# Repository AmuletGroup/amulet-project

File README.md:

The Amulet Project
=====

**The Amulet Project** envisions computational jewelry, in the form of a bracelet or pendant, that provide the properties essential for successful body-area mHealth networks. These devices coordinate the activity of the body-area network and provide a discreet means for communicating with their wearer. Such devices complement the capabilities of a smartphone, bridging the gap between the type of pervasive computing possible with a mobile phone and that enabled by wearable computing. Find more information on the [Amulet Project Website](https://amulet-project.org/)

**The Amulet Platform** is a major step towards fulfilling this vision. The generalized platform is comprised of hardware and software for developing energy- and resource-efficient applications on multi-application wearable devices. This includes:

- the Amulet Firmware Toolchain
- the Amulet Runtime
- the ARP-View energy prediction and insight graphical tool ([check out a demo here](https://arpview.herokuapp.com))
- open reference hardware.

Amulet allows developers to interactively explore how their implementation decisions impact battery life without the need for hardware modeling and additional software development. **Amulet represents a new approach to developing long-lived wearable applications.** We envision the Amulet Platform enabling long-duration experiments on human subjects in a wide variety of studies.

We also aim to equip the health-behavior science community with a wearable platform researchers can field for long-duration experiments on human subjects in a wide variety of studies, by providing the entire Amulet Platform as an open-source, open-hardware alternative to the available commercial platforms that have so far been used for wearables research. 
We envision the Amulet Platform as being broadly applicable to those in the sensing communities, as well as domain scientists and practitioners in human-centered fields like health and fitness. With the Amulet Platform, sensor researchers can prototype new wearable devices and test new sensing technology without building from scratch.

---

### Getting Started
To learn how to obtain hardware, setup your dev environment, and program an Amulet refer to [this](GETTING_STARTED.md) guide.

---

### Contributors and Acknowledgements
Amulet is an ongoing collaboration between Dartmouth College and Clemson University.

**Dartmouth College:**

- Ryan Halter (Engineering): Co-PI; Assistant Professor of Engineering.
- David Kotz (Computer Science): Principal Investigator; Professor of Computer Science.
- John Batsis (Geisel School Of Medicine)
- Taylor Hardin (Computer Science): graduate student.
- Sarah Lord (Psychiatric Research Center)
- Jasmine Mai (Computer Science): undergraduate student.
- Varun Mishra (Computer Science): graduate student.
- Patrick Proctor (Computer Science): programmer.
- Ron Peterson (Computer Science): senior programmer.
- Gunnar Pope (Engineering): graduate student.

**Clemson University:**

- Kelly Caine (Human Centered Computing): Co-PI; Assistant Professor of Human-Centered Computing.
- Josiah Hester (Computer Science): graduate student, now at Northwestern.
- Vivian Motti (Human Centered Computing): now at George Mason University.
- Ryan Scott (Computer Science: Graduate Student.
- Jacob Sorber (Computer Science): PI; Assistant Professor of Computer Science.
- Byron Lowens (Human Centered Computing): graduate student.

**Former members:**

- George Boateng (Engineering): graduate student; now at ETH Zurich.
- Eric Chen (Computer Science): undergraduate student.
- Kevin Freeman (Computer Science): graduate student.
- Bhargav Golla (Computer Science): graduate student.
- Emily Greene (Computer Science): undergraduate student; now at Amazon.
- Steven Hearndon (Computer Science): graduate student.
- Hilary Johnson (Engineering): undergraduate student.
- Anna Knowles (Computer Science): undergraduate student.
- Andrés Molina-Markham (Computer Science); now at RSA Labs.
- Emma Oberstein (Computer Science): undergraduate student.
- Travis Peters (Computer Science): graduate student.
- Joseph Skinner (Engineering): technician.
- Tianlong Yun (Computer Science): now at Google.

This research results from a research program at the Institute for Security, Technology, and Society, supported by the National Science Foundation under award numbers CNS- 1314281, CNS-1314342, and TC-0910842, and by the Department of Health and Human Services (SHARP program) under award number 90TR0003-01. The views and conclusions contained in this document are those of the authors and should not be interpreted as necessarily representing the official policies, either expressed or implied, of the sponsors.

---
### License

```
Copyright 2016 by the Trustees of Dartmouth College and Clemson University, 
and distributed under the terms of the "Dartmouth College Non-Exclusive Research
Use Source Code License Agreement" (for NON-COMMERCIAL research purposes only), 
as detailed in a file named LICENSE.pdf within this repository.
```
[Please find our full license here.](LICENSE.pdf)

---
### Attribution

Please find a list of software used in the development of Amulet [here.](ATTRIBUTION.md)

---
### Issues

Please use Github's Issue tracking software to submit any issues or concerns regarding Amulet software or hardware.

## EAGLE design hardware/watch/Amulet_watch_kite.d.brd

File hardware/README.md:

Hardware
===
The Amulet wearable prototype is mostly a single-board system. 
The main board, battery, haptic buzzer, and secondary storage board are all housed in a custom-designed 3D-printed case that fits a standard 20mm off-the-shelf watchband.

#### Features
- **Processing**: 
  - Texas Instruments MSP430FR5989, 2 KB SRAM and 128 KB of FRAM
- **Sensing**: 
  - Analog Devices ADMP510 microphone
  - Everlight ALS-PT19 light sensor
  - Texas Instruments TMP20 temperature sensor
  - STMicroelectronics LSM6DSL gyroscope
  - Analog Devices ADXL362 accelerometer
  - Lapis Semi ML8511 UVA/B sensor
- **Communication**: 
  - Nordic nRF51822 used as a modem for communicating with peripheral BLE devices (such as a heart-rate monitor)
- **User Interface**: 
  - Sharp LS013B7DH03 display with 128x128 resolution
  - Two buttons
  - Three capacitive touch sensors with low power MPR121 touch controller
  - Haptic buzzer, and two LEDs.
- **Storage**:  
 - The small secondary storage board holds a microSD card reader. 
- **Misc**:
  - The board also includes a battery charger (MCP73831)
  - 110mAh battery

### Getting an Amulet
You can build your own using the hardware files provided or request pre-built Amulet's from us by contacting rapjr@cs.dartmouth.edu. If you are part of a research lab we will generally accept your request.

### Assembling an Amulet
Refer to [this](../media/Amulet_DC_kitec_assembly.pdf) guide for assembling the Amulet companion board, and [this](../media/Amulet_kitec_case_assembly.pdf) guide for placing an amulet in a case.

### Programming an Amulet
[Refer to this guide for how to set up your dev environment and program an amulet.](../GETTING_STARTED.md)

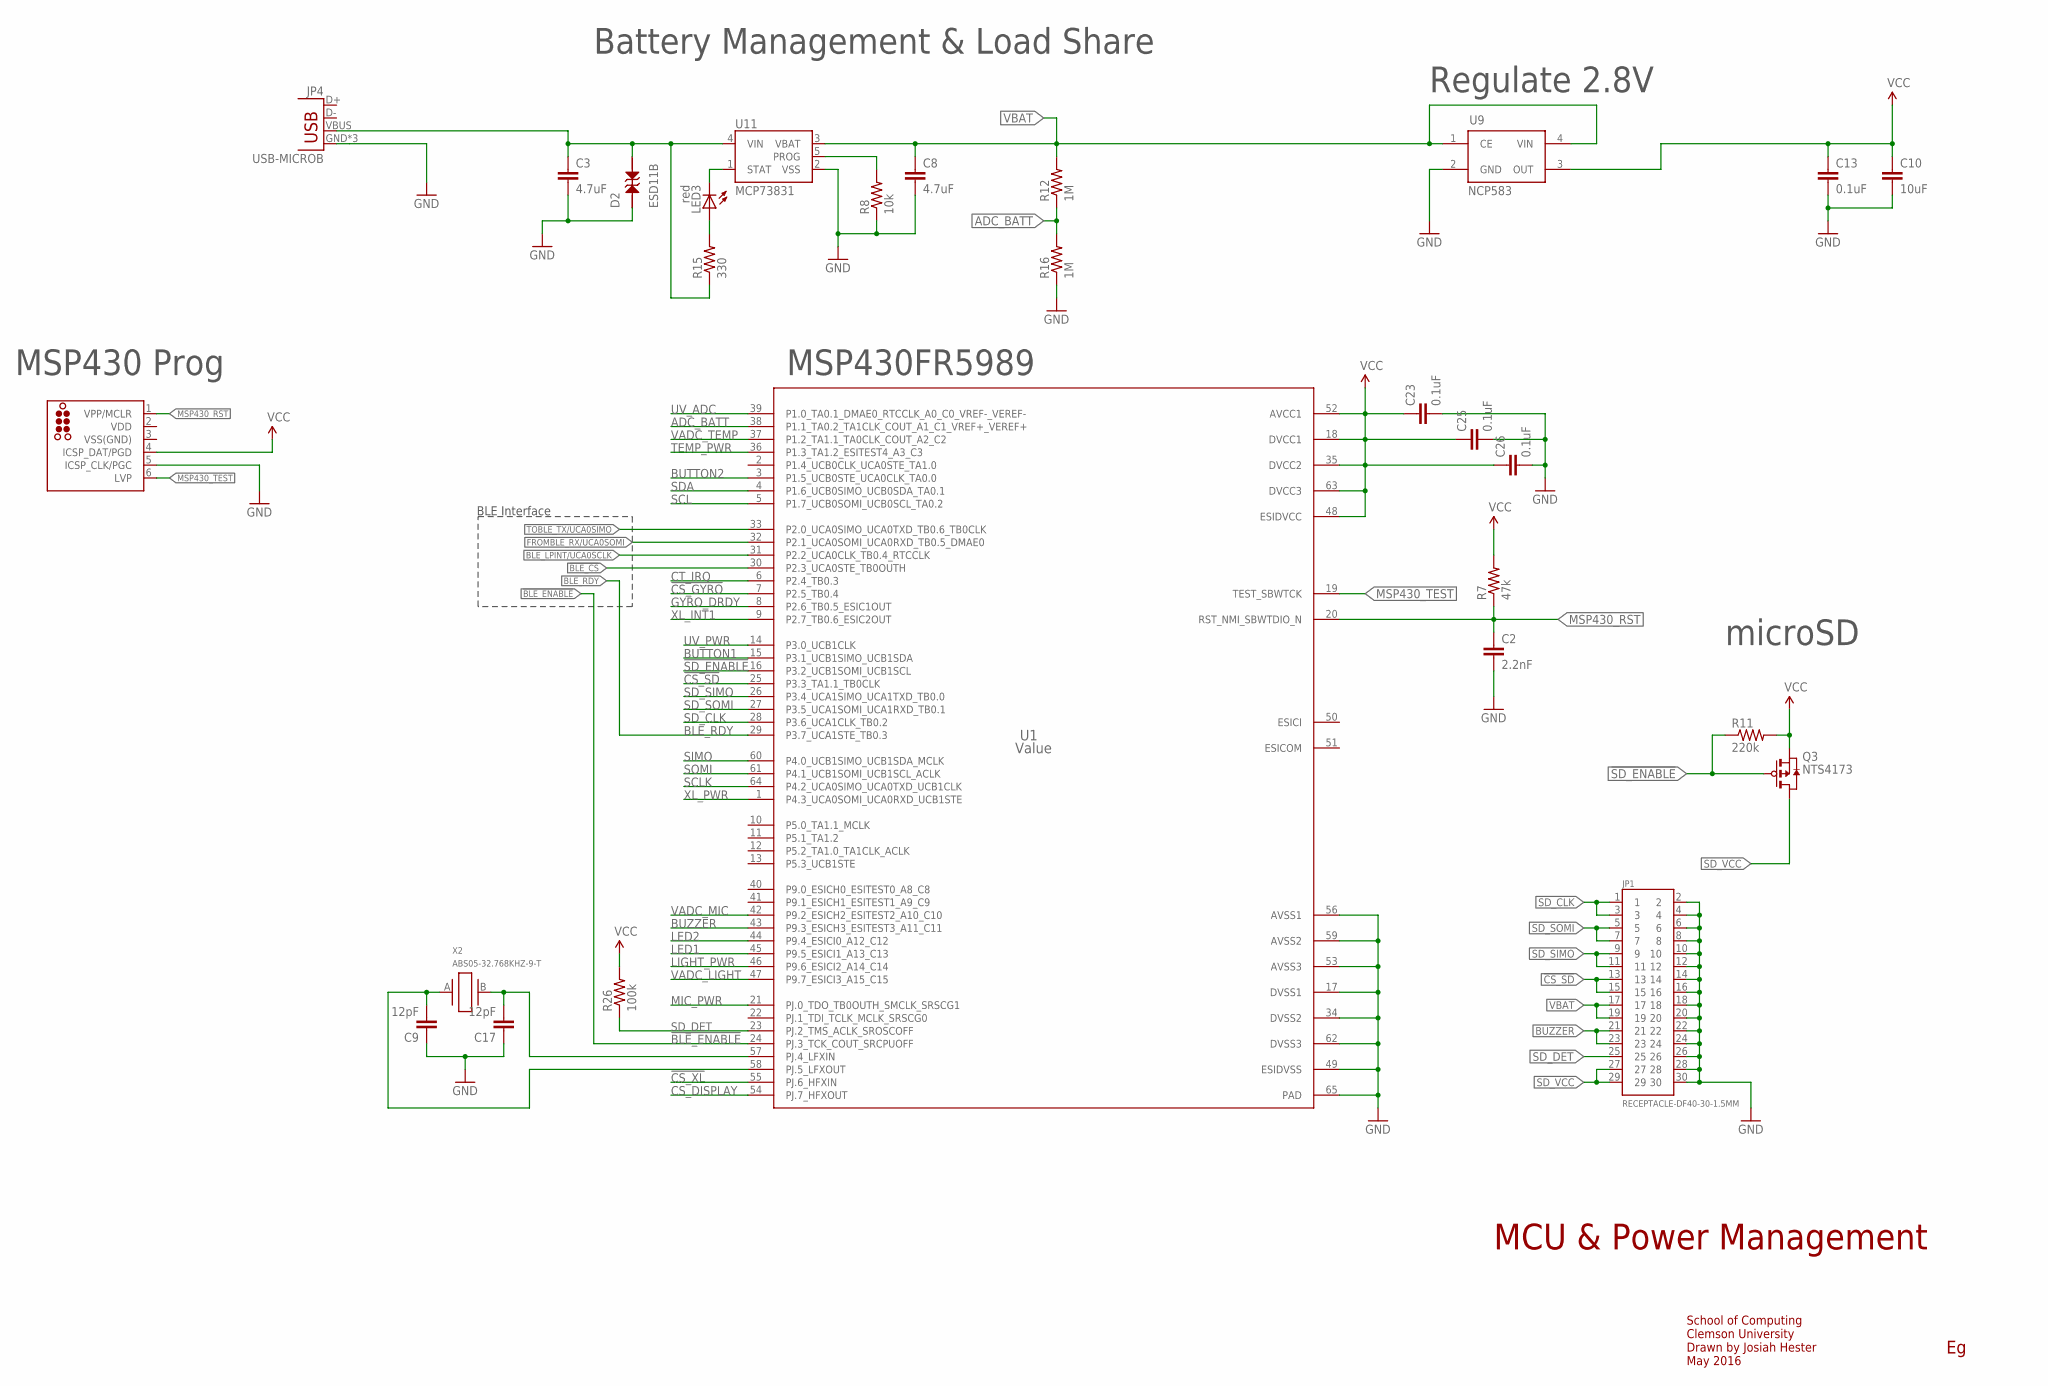
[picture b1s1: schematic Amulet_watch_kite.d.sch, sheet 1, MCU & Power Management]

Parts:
C2: 2.2nF; 0402
C3, C8: 4.7uF; 0805
C9, C17: 12pF; 0402
C10: 10uF; 0805
C13, C23, C25, C26: 0.1uF; 0402
D2: ESD11B; DSN2
J1: TC2030-MCP-NL
JP1: RECEPTACLE-DF40-30-1.5MM
JP4: USB-MICROB
LED3: red; LED-0603
Q3: NTS4173; SC-70-3
R7: 47k; 0402
R8: 10k; 0402
R11: 220k; 0402; DIGIKEY RHM12.0KCDCT-ND
R12, R16: 1M; 0402
R15: 330; 0402
R26: 100k; 0402
U1: Value; RGC0064B; DIGIKEY 296-42031-1-ND
U9: NCP583; SC82-AB_1PRIMARY
U11: MCP73831; SOT23-5
X2: ABS05-32.768KHZ-9-T; ABS05

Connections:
!BLE_CS: U1.30 (P2.3_UCA0STE_TB0OUTH); also elsewhere on the board
!BLE_ENABLE: U1.24 (PJ.3_TCK_COUT_SRCPUOFF); also elsewhere on the board
!CS_GYRO: U1.7 (P2.5_TB0.4); also elsewhere on the board
!CS_SD: JP1.13, JP1.15, U1.25 (P3.3_TA1.1_TB0CLK)
!CS_XL: U1.55 (PJ.6_HFXIN); also elsewhere on the board
!SD_ENABLE: Q3.P1 (G), R11.1, U1.16 (P3.2_UCB1SOMI_UCB1SCL)
ADC_BATT: R12.1, R16.2, U1.38 (P1.1_TA0.2_TA1CLK_COUT_A1_C1_VREF+_VERE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)
BLE_LPINT/UCA0SCLK: U1.31 (P2.2_UCA0CLK_TB0.4_RTCCLK); also elsewhere on the board
BLE_RDY: U1.29 (P3.7_UCA1STE_TB0.3); also elsewhere on the board
BUTTON1: U1.15 (P3.1_UCB1SIMO_UCB1SDA); also elsewhere on the board
BUTTON2: U1.3 (P1.5_UCB0STE_UCA0CLK_TA0.0); also elsewhere on the board
BUZZER: JP1.21, JP1.23, U1.43 (P9.3_ESICH3_ESITEST3_A11_C11)
CS_DISPLAY: U1.54 (PJ.7_HFXOUT); also elsewhere on the board
CT_IRQ: U1.6 (P2.4_TB0.3); also elsewhere on the board
FROMBLE_RX/UCA0SOMI: U1.32 (P2.1_UCA0SOMI_UCA0RXD_TB0.5_DMAE0); also elsewhere on the board
GND: C2.2, C3.2, C8.2, C9.1, C10.2, C13.2, C17.1, C23.2, C25.2, C26.2, D2.P$1 (1), J1.5 (ICSP_CLK/PGC), JP1.2, JP1.4, JP1.6, JP1.8, JP1.10, JP1.12, JP1.14, JP1.16, JP1.18, JP1.20, JP1.22, JP1.24, JP1.26, JP1.28, JP1.30, JP4.GND, JP4.MT1 (GND), JP4.MT2 (GND), R8.1, R16.1, U1.17 (DVSS1), U1.34 (DVSS2), U1.49 (ESIDVSS), U1.53 (AVSS3), U1.56 (AVSS1), U1.59 (AVSS2), U1.62 (DVSS3), U1.65 (PAD), U9.2 (GND), U11.2 (VSS); also elsewhere on the board
GYRO_DRDY: U1.8 (P2.6_TB0.5_ESIC1OUT); also elsewhere on the board
LED1: U1.45 (P9.5_ESICI1_A13_C13); also elsewhere on the board
LED2: U1.44 (P9.4_ESICI0_A12_C12); also elsewhere on the board
LIGHT_PWR: U1.46 (P9.6_ESICI2_A14_C14); also elsewhere on the board
MIC_PWR: U1.21 (PJ.0_TDO_TB0OUTH_SMCLK_SRSCG1); also elsewhere on the board
MSP430_RST: C2.1, J1.1 (VPP/MCLR), R7.1, U1.20 (RST_NMI_SBWTDIO_N); also elsewhere on the board
MSP430_TEST: J1.6 (LVP), U1.19 (TEST_SBWTCK)
unnamed: R8.2, U11.5 (PROG)
unnamed: C17.2, U1.57 (PJ.4_LFXIN), X2.B (2)
unnamed: C9.2, U1.58 (PJ.5_LFXOUT), X2.A (1)
unnamed: LED3.C, U11.1 (STAT)
unnamed: LED3.A, R15.2
SCL: U1.5 (P1.7_UCB0SOMI_UCB0SCL_TA0.2); also elsewhere on the board
SCLK: U1.64 (P4.2_UCA0SIMO_UCA0TXD_UCB1CLK); also elsewhere on the board
SDA: U1.4 (P1.6_UCB0SIMO_UCB0SDA_TA0.1); also elsewhere on the board
SD_CLK: JP1.1, JP1.3, U1.28 (P3.6_UCA1CLK_TB0.2)
SD_DET: JP1.25, R26.1, U1.23 (PJ.2_TMS_ACLK_SROSCOFF)
SD_SIMO: JP1.9, JP1.11, U1.26 (P3.4_UCA1SIMO_UCA1TXD_TB0.0)
SD_SOMI: JP1.5, JP1.7, U1.27 (P3.5_UCA1SOMI_UCA1RXD_TB0.1)
SD_VCC: JP1.27, JP1.29, Q3.P3 (D)
SIMO: U1.60 (P4.0_UCB1SIMO_UCB1SDA_MCLK); also elsewhere on the board
SOMI: U1.61 (P4.1_UCB1SOMI_UCB1SCL_ACLK); also elsewhere on the board
TEMP_PWR: U1.36 (P1.3_TA1.2_ESITEST4_A3_C3); also elsewhere on the board
TOBLE_TX/UCA0SIMO: U1.33 (P2.0_UCA0SIMO_UCA0TXD_TB0.6_TB0CLK); also elsewhere on the board
UV_ADC: U1.39 (P1.0_TA0.1_DMAE0_RTCCLK_A0_C0_VREF-_VER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); also elsewhere on the board
UV_PWR: U1.14 (P3.0_UCB1CLK); also elsewhere on the board
VADC_LIGHT: U1.47 (P9.7_ESICI3_A15_C15); also elsewhere on the board
VADC_MIC: U1.42 (P9.2_ESICH2_ESITEST2_A10_C10); also elsewhere on the board
VADC_TEMP: U1.37 (P1.2_TA1.1_TA0CLK_COUT_A2_C2); also elsewhere on the board
VBAT: C8.1, JP1.17, JP1.19, R12.2, U9.1 (CE), U9.4 (VIN), U11.3 (VBAT)
VCC: C10.1, C13.1, C23.1, C25.1, C26.1, J1.4 (ICSP_DAT/PGD), Q3.P2 (S), R7.2, R11.2, R26.2, U1.18 (DVCC1), U1.35 (DVCC2), U1.48 (ESIDVCC), U1.52 (AVCC1), U1.63 (DVCC3), U9.3 (OUT); also elsewhere on the board
VDD: J1.2 (VDD)
VIN: C3.1, D2.P$2 (2), JP4.VBUS, R15.1, U11.4 (VIN)
VSS(GND): J1.3 (VSS(GND))
XL_INT1: U1.9 (P2.7_TB0.6_ESIC2OUT); also elsewhere on the board
XL_PWR: U1.1 (P4.3_UCA0SOMI_UCA0RXD_UCB1STE); also elsewhere on the board

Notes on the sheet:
MCU & Power Management
School of Computing Clemson University Drawn by Josiah Hester May 2016
MSP430FR5989
Regulate 2.8V
Battery Management & Load Share
microSD
BLE Interface
MSP430 Prog

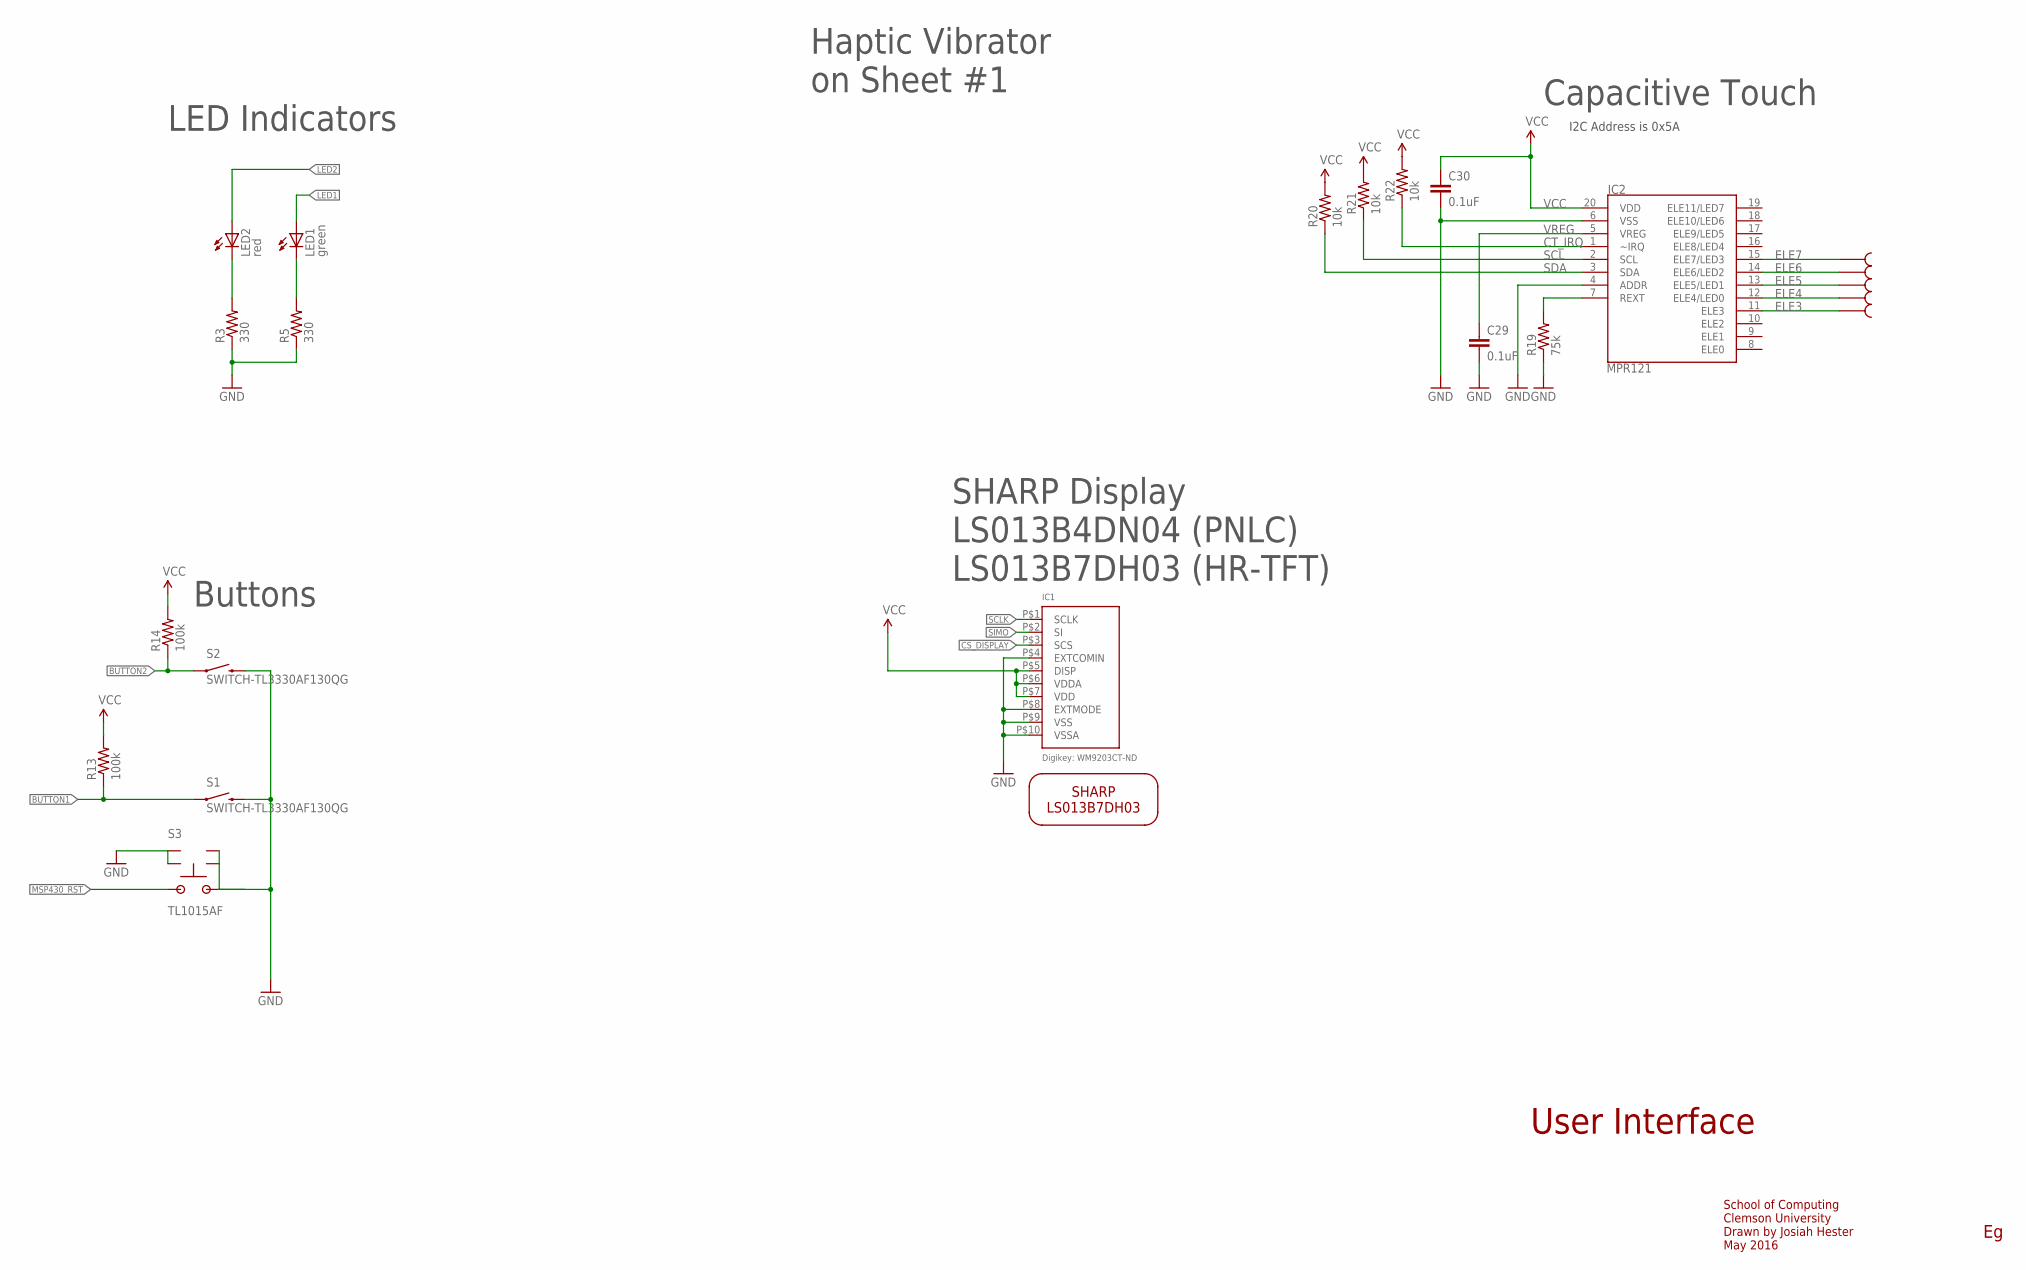
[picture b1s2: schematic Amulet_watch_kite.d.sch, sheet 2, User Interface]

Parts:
C29, C30: 0.1uF; 0402
IC1: Digikey: WM9203CT-ND; FPC_10PIN_52892-1095
IC2: MPR121; QFN-20-0.4MM-V2
LED1: green; LED-0603
LED2: red; LED-0603
R3, R5: 330; 0402
R13, R14: 100k; 0402
R19: 75k; 0402; DIGIKEY 311-75KLRCT-ND
R20, R21, R22: 10k; 0402
S1: SWITCH-TL3330AF130QG; TL3330AF130QG
S2: SWITCH-TL3330AF130QG; TL3330AF130QG; DIGIKEY EG4388CT-ND
S3: TL1015AF; TS1015
U$3: LS013B7DH03; LS013B7DH03_HF
U$6, U$7, U$8, U$9, U$10: CTPAD

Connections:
BUTTON1: R13.1, S1.2; also elsewhere on the board
BUTTON2: R14.1, S2.2; also elsewhere on the board
CS_DISPLAY: IC1.P$3 (SCS); also elsewhere on the board
CT_IRQ: IC2.1 (~IRQ), R22.1; also elsewhere on the board
ELE3: IC2.11 (ELE3), U$10.P$1
ELE4: IC2.12 (ELE4/LED0), U$9.P$1
ELE5: IC2.13 (ELE5/LED1), U$8.P$1
ELE6: IC2.14 (ELE6/LED2), U$7.P$1
ELE7: IC2.15 (ELE7/LED3), U$6.P$1
GND: C29.2, C30.2, IC1.P$4 (EXTCOMIN), IC1.P$8 (EXTMODE), IC1.P$9 (VSS), IC1.P$10 (VSSA), IC2.4 (ADDR), IC2.6 (VSS), R3.1, R5.1, R19.1, S1.1, S2.1, S3.1, S3.G1 (GND), S3.G2 (GND), S3.G3 (GND), S3.G4 (GND); also elsewhere on the board
LED1: LED1.A; also elsewhere on the board
LED2: LED2.A; also elsewhere on the board
MSP430_RST: S3.2; also elsewhere on the board
unnamed: LED2.C, R3.2
unnamed: LED1.C, R5.2
REXT: IC2.7 (REXT), R19.2
SCL: IC2.2 (SCL), R21.1; also elsewhere on the board
SCLK: IC1.P$1 (SCLK); also elsewhere on the board
SDA: IC2.3 (SDA), R20.1; also elsewhere on the board
SIMO: IC1.P$2 (SI); also elsewhere on the board
VCC: C30.1, IC1.P$5 (DISP), IC1.P$6 (VDDA), IC1.P$7 (VDD), IC2.20 (VDD), R13.2, R14.2, R20.2, R21.2, R22.2; also elsewhere on the board
VREG: C29.1, IC2.5 (VREG)

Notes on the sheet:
User Interface
School of Computing Clemson University Drawn by Josiah Hester May 2016
SHARP Display LS013B4DN04 (PNLC) LS013B7DH03 (HR-TFT)
LED Indicators
Capacitive Touch
Buttons
Haptic Vibrator on Sheet #1
I2C Address is 0x5A

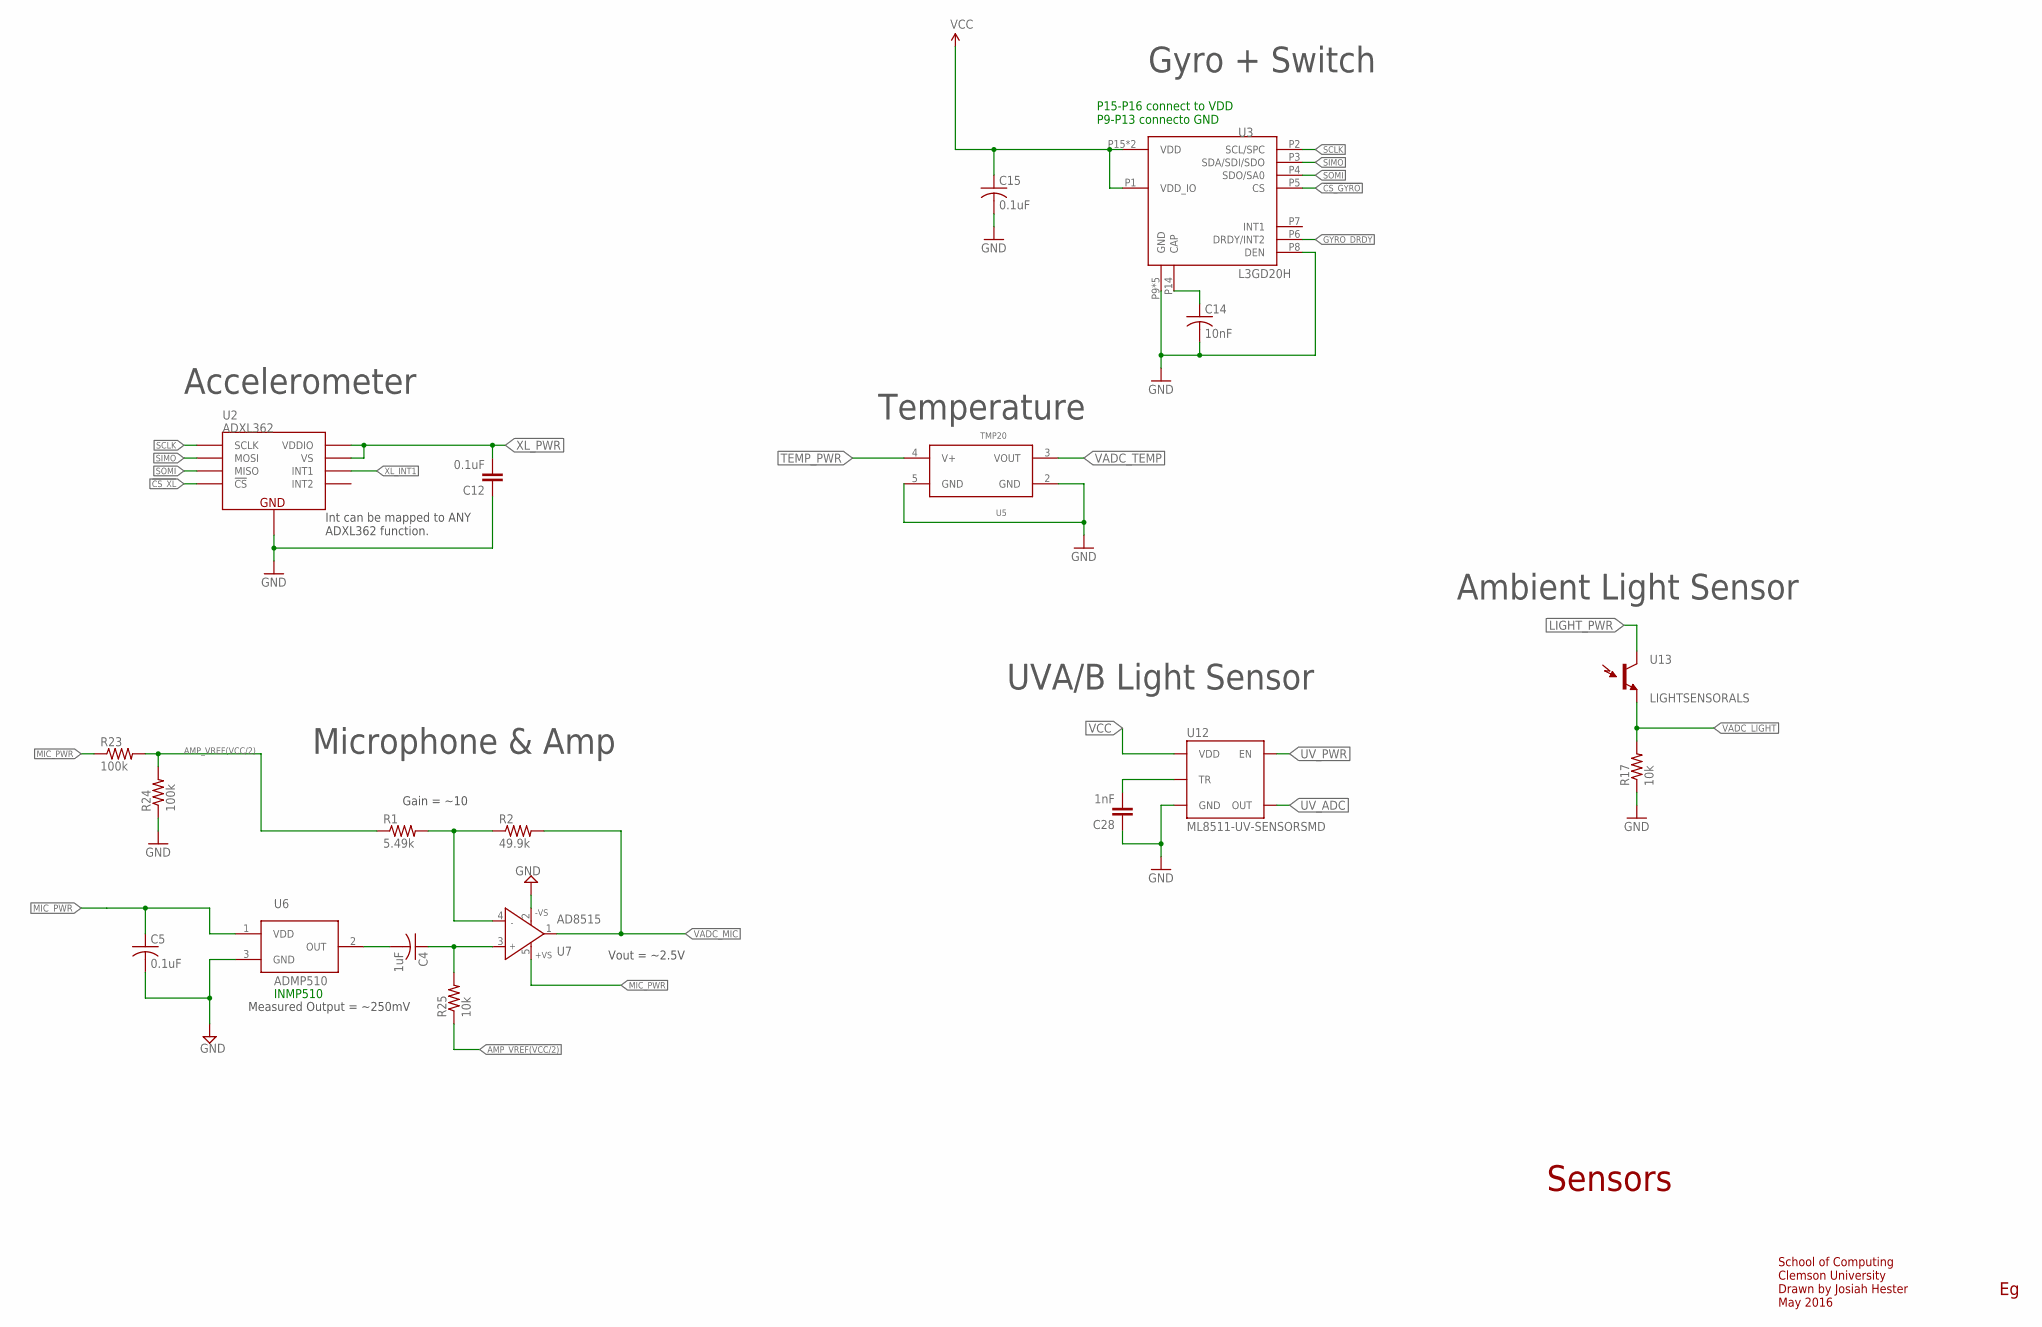
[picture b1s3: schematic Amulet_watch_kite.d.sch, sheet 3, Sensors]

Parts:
C4: 1uF; 0402
C5, C12, C15: 0.1uF; 0402
C14: 10nF; 0402
C28: 1nF; 0402
R1: 5.49k; 0402
R2: 49.9k; 0402
R17: 10k; 0402; DIGIKEY 311-4.7KJRCT-ND
R23, R24: 100k; 0402
R25: 10k; 0402
U2: ADXL362
U3: L3GD20H; LGA16L
U5: TMP20; SC70-5L
U6: ADMP510
U7: AD8515; SOT23-5
U12: ML8511-UV-SENSORSMD; ML8511
U13: LIGHTSENSORALS; ALS-PT19; DIGIKEY 1080-1244-1-ND

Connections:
!CS_GYRO: U3.P5 (CS); also elsewhere on the board
!CS_XL: U2.P$8 (!CS); also elsewhere on the board
AMP_VREF(VCC/2): R1.P$1 (1), R23.P$2 (2), R24.P$2 (2), R25.P$1 (1)
GND: C5.P$2 (2), C12.1, C14.P$2 (2), C15.P$2 (2), C28.1, R17.P$1 (1), R24.P$1 (1), U2.P$12 (GND), U2.P$13 (GND), U2.P$16 (GND), U3.P8 (DEN), U3.P9 (GND), U3.P10 (GND), U3.P11 (GND), U3.P12 (GND), U3.P13 (GND), U5.2 (GND), U5.5 (GND), U6.3 (GND), U7.2 (-VS), U12.5 (GND); also elsewhere on the board
GYRO_DRDY: U3.P6 (DRDY/INT2); also elsewhere on the board
LIGHT_PWR: U13.C (C1); also elsewhere on the board
MIC_AMP-: R1.P$2 (2), R2.P$1 (1), U7.4 (IN-)
MIC_OUT: C4.P$2 (2), U6.2 (OUT)
MIC_PWR: C5.P$1 (1), R23.P$1 (1), U6.1 (VDD), U7.5 (+VS); also elsewhere on the board
unnamed: C14.P$1 (1), U3.P14 (CAP)
unnamed: C28.2, U12.10 (TR)
unnamed: C4.P$1 (1), R25.P$2 (2), U7.3 (IN+)
SCLK: U2.P$4 (SCLK), U3.P2 (SCL/SPC); also elsewhere on the board
SIMO: U2.P$6 (MOSI), U3.P3 (SDA/SDI/SDO); also elsewhere on the board
SOMI: U2.P$7 (MISO), U3.P4 (SDO/SA0); also elsewhere on the board
TEMP_PWR: U5.4 (V+); also elsewhere on the board
UV_ADC: U12.8 (OUT); also elsewhere on the board
UV_PWR: U12.4 (EN); also elsewhere on the board
VADC_LIGHT: R17.P$2 (2), U13.E (E1); also elsewhere on the board
VADC_MIC: R2.P$2 (2), U7.1 (OUT); also elsewhere on the board
VADC_TEMP: U5.3 (VOUT); also elsewhere on the board
VCC: C15.P$1 (1), U3.P1 (VDD_IO), U3.P15 (VDD), U3.P16 (VDD), U12.7 (VDD); also elsewhere on the board
XL_INT1: U2.P$11 (INT1); also elsewhere on the board
XL_PWR: C12.2, U2.P$1 (VDDIO), U2.P$14 (VS); also elsewhere on the board

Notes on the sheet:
Sensors
Microphone & Amp
Ambient Light Sensor
Measured Output = ~250mV
Vout = ~2.5V
Gain = ~10
Accelerometer
Gyro + Switch
School of Computing Clemson University Drawn by Josiah Hester May 2016
Temperature
UVA/B Light Sensor
Int can be mapped to ANY ADXL362 function.
P15-P16 connect to VDD P9-P13 connecto GND
INMP510

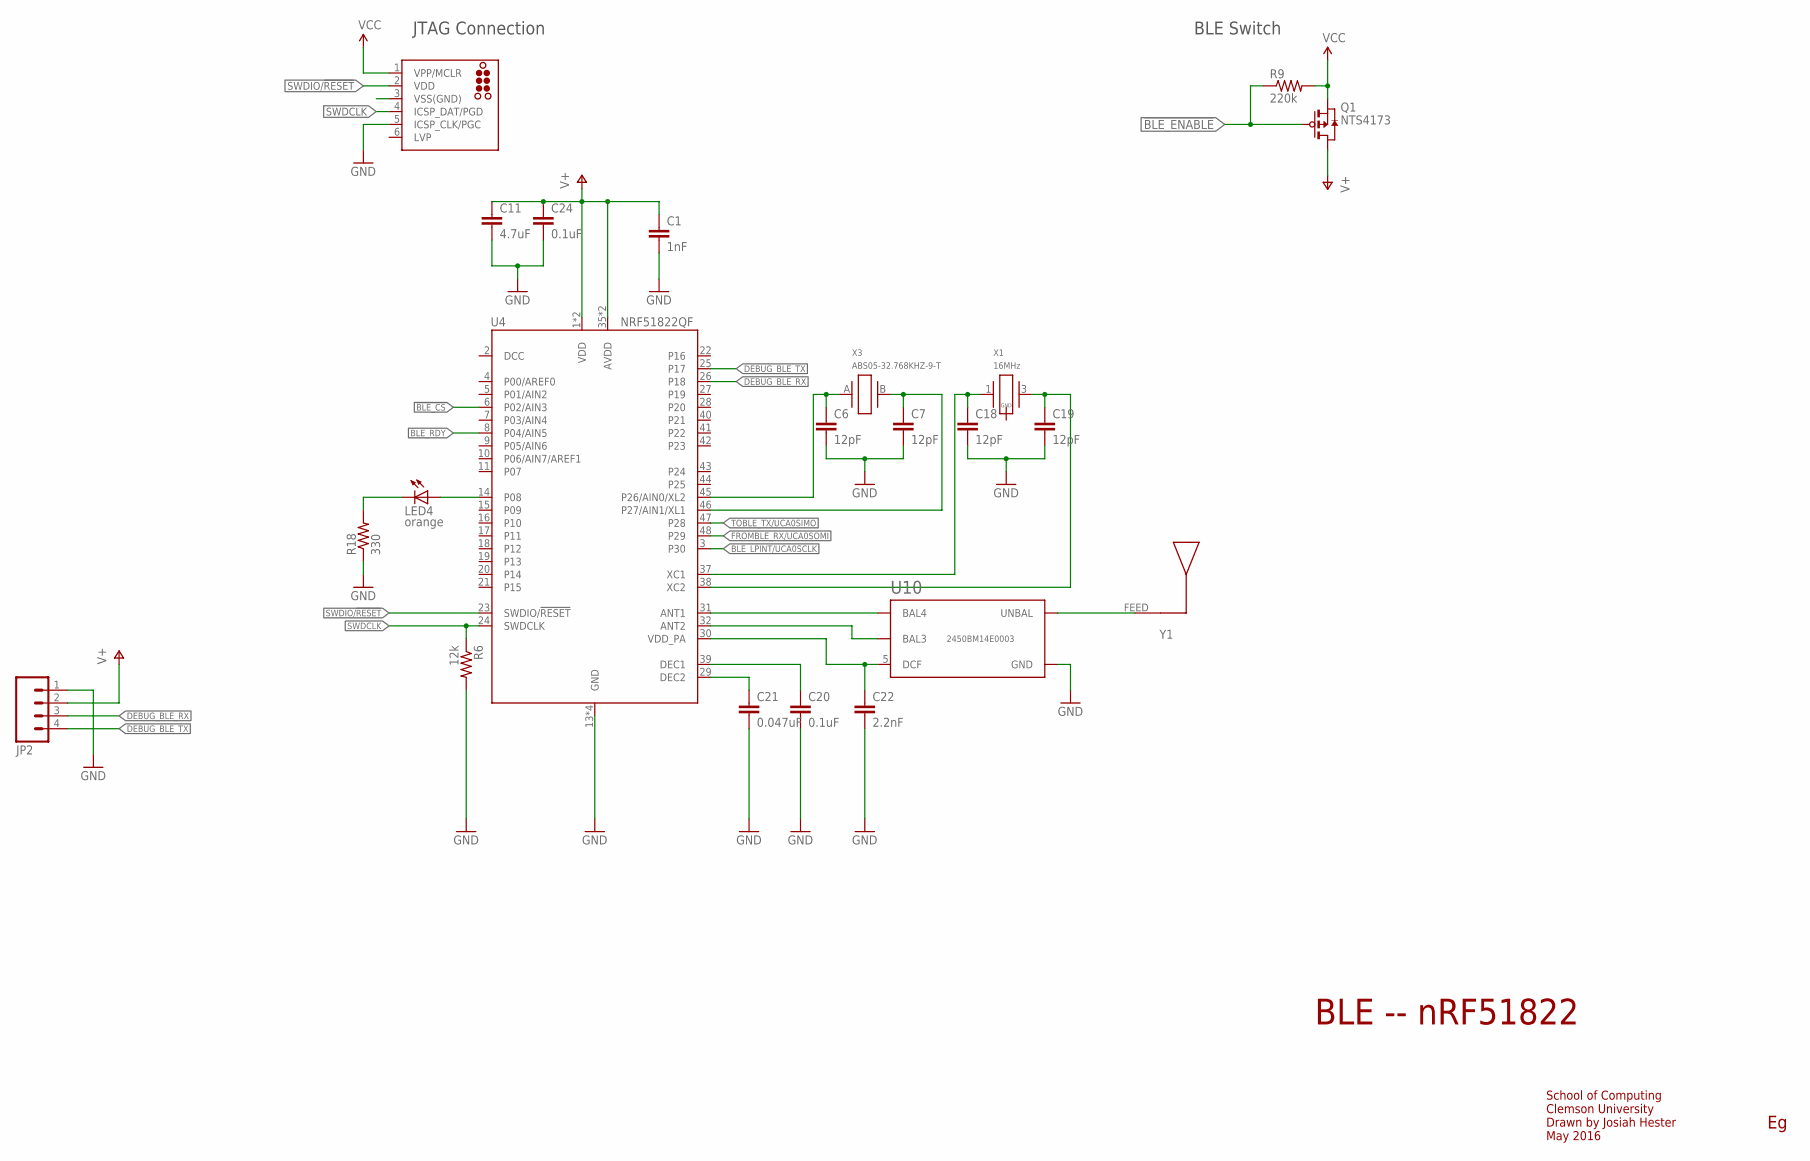
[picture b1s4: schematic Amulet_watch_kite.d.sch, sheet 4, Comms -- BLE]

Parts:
C1: 1nF; 0402; DIGIKEY 490-1303-1-ND
C6, C7, C18, C19: 12pF; 0402; DIGIKEY 490-6197-1-ND
C11: 4.7uF; 0805; DIGIKEY 445-5947-1-ND
C20: 0.1uF; 0402; DIGIKEY 490-1303-1-ND
C21: 0.047uF; 0402; DIGIKEY 445-1264-1-ND
C22: 2.2nF; 0402; DIGIKEY 490-5419-1-ND
C24: 0.1uF; 0402; DIGIKEY 445-4952-1-ND
J3: TC2030-NODRILLS; TC2030-MCP-NODRILLS
JP2: M041.27MM; 1X04-1.27MM
LED4: orange; LED-0603; DIGIKEY 160-1445-1-ND
Q1: NTS4173; SC-70-3
R6: 12k; 0402; DIGIKEY RHM12.0KCDCT-ND
R9: 220k; 0402; DIGIKEY RHM12.0KCDCT-ND
R18: 330; 0402
U4: NRF51822QF; QFN-48-6MM; DIGIKEY 1490-1042-1-ND
U10: 2450BM14E0003
X1: 16MHz; TXC-8Y; DIGIKEY 887-2003-1-ND
X3: ABS05-32.768KHZ-9-T; ABS05
Y1: 2450AT42A100E; 2450AT42A100; DIGIKEY 712-1007-1-ND

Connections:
!BLE_CS: U4.6 (P02/AIN3); also elsewhere on the board
!BLE_ENABLE: Q1.P1 (G), R9.1; also elsewhere on the board
BLE_LPINT/UCA0SCLK: U4.3 (P30); also elsewhere on the board
BLE_RDY: U4.8 (P04/AIN5); also elsewhere on the board
DEBUG_BLE_RX: JP2.3, U4.26 (P18)
DEBUG_BLE_TX: JP2.4, U4.25 (P17)
FROMBLE_RX/UCA0SOMI: U4.48 (P29); also elsewhere on the board
GND: C1.2, C6.2, C7.2, C11.2, C18.2, C19.2, C20.2, C21.2, C22.2, C24.2, J3.5 (ICSP_CLK/PGC), JP2.1, R6.2, R18.1, U4.13 (GND), U4.33 (GND), U4.34 (GND), U4.GND, U10.2 (GND), U10.6 (GND); also elsewhere on the board
unnamed: U10.1 (UNBAL), Y1.FEED
unnamed: C22.1, U4.30 (VDD_PA), U10.5 (DCF)
unnamed: U4.31 (ANT1), U10.4 (BAL4)
unnamed: C6.1, U4.45 (P26/AIN0/XL2), X3.A (1)
unnamed: C7.1, U4.46 (P27/AIN1/XL1), X3.B (2)
unnamed: U4.32 (ANT2), U10.3 (BAL3)
unnamed: C18.1, U4.37 (XC1), X1.1
unnamed: C19.1, U4.38 (XC2), X1.3 (2)
unnamed: C20.1, U4.39 (DEC1)
unnamed: C21.1, U4.29 (DEC2)
unnamed: LED4.C, R18.2
unnamed: LED4.A, U4.14 (P08)
NNUNOAUSDOASND: J3.3 (VSS(GND))
SWDCLK: J3.4 (ICSP_DAT/PGD), R6.1, U4.24 (SWDCLK)
SWDIO/!RESET: J3.2 (VDD), U4.23 (SWDIO/!RESET)
TOBLE_TX/UCA0SIMO: U4.47 (P28); also elsewhere on the board
V+: C1.1, C11.1, C24.1, JP2.2, Q1.P3 (D), U4.1 (VDD), U4.12 (VDD), U4.35 (AVDD), U4.36 (AVDD)
VCC: J3.1 (VPP/MCLR), Q1.P2 (S), R9.2; also elsewhere on the board

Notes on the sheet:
BLE -- nRF51822
School of Computing Clemson University Drawn by Josiah Hester May 2016
BLE Switch
JTAG Connection

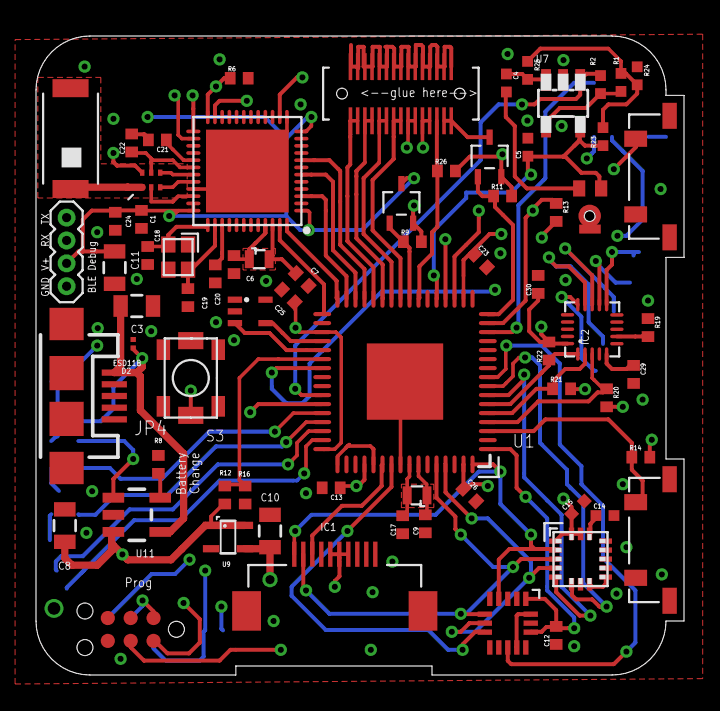
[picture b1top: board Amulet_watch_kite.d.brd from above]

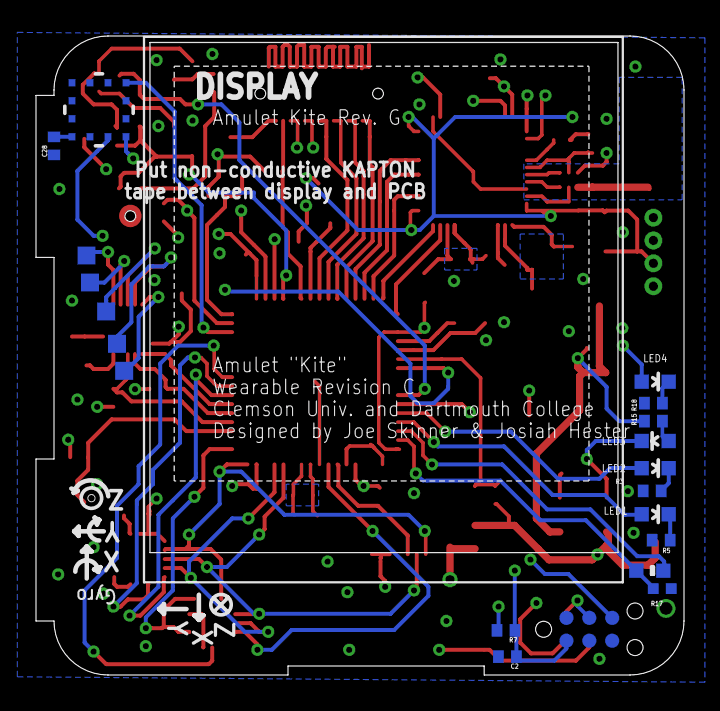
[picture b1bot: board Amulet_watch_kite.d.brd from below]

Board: 4 copper layers, 36.0 x 35.5 mm, 91 parts (21 on the bottom side), 82 nets.

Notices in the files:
parts and their libraries:
SparkFun-Connectors: Licensing: Creative Commons ShareAlike 4.0 International - https://creativecommons.org/licenses/by-sa/4.0
SparkFun-Aesthetics: Licensing: CC v3.0 Share-Alike You are welcome to use this library for commercial purposes.
